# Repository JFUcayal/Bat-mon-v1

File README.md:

# Bat-mon-v1
**Edge Device for Battery Environment Monitoring System (Lithium Storage and Transport)**

- **Bat-Mon** is a hardware/firmware project developed as part of my Master's thesis in an industrial environment at [b.again](https://b.again.pt/pt_PT/) [(dstgroup)](https://www.dstsgps.com/intro-pt-pt/#/#intro), focused on the real-time monitoring of lithium batteries. 
- It includes custom-designed PCBs for fixed and portable use cases, enabling the detection of environmental conditions such as **temperature**, **humidity**, and **vibration**. All hardware was developed using **KiCAD**.
- This project was developed in the context of a national R&D consortium for advanced energy storage systems:  
[New Generation Storage](https://newgenstorage.pt). It is partially funded by the **PRR – Recovery and Resilience Plan** and aims to support innovation in battery safety and smart monitoring systems.

## 🔧 Project Overview

Lithium batteries, whether in stationary storage or during transport, require careful environmental monitoring to ensure safety. Bat-Mon addresses this need by providing two types of monitoring devices:

- **Stationary Unit**: Designed for static storage. Measures temperature and humidity.
- **Portable Unit**: Designed for battery transport scenarios. Measures temperature, humidity, and vibration.

Both units support low-power operation and are intended to be integrated into broader telemetry or management systems.

## 📟 3D Views of the PCBs
<div id="image-table" align="center">
    <table>
        <tr>
            <td style="padding:10px"> <strong>📦 Stationary Monitoring Prototype</strong><br/><br/>
                
            </td>
            <td style="padding:10px"> <br/><strong>🚚 Portable Monitoring Prototype</strong><br/><br/>
                 
            </td>
        </tr>
    </table>
</div>
    
## 🚀 Key Features

- 🌡️ **Temperature and Humidity Sensing**
- 📈 **Vibration Detection** (portable unit)
- 📶 **BLE Communication Support**
- 🔋 **Low Power Design**
- 📐 **Designed in KiCAD**
- 🧠 **Powered by STM32**

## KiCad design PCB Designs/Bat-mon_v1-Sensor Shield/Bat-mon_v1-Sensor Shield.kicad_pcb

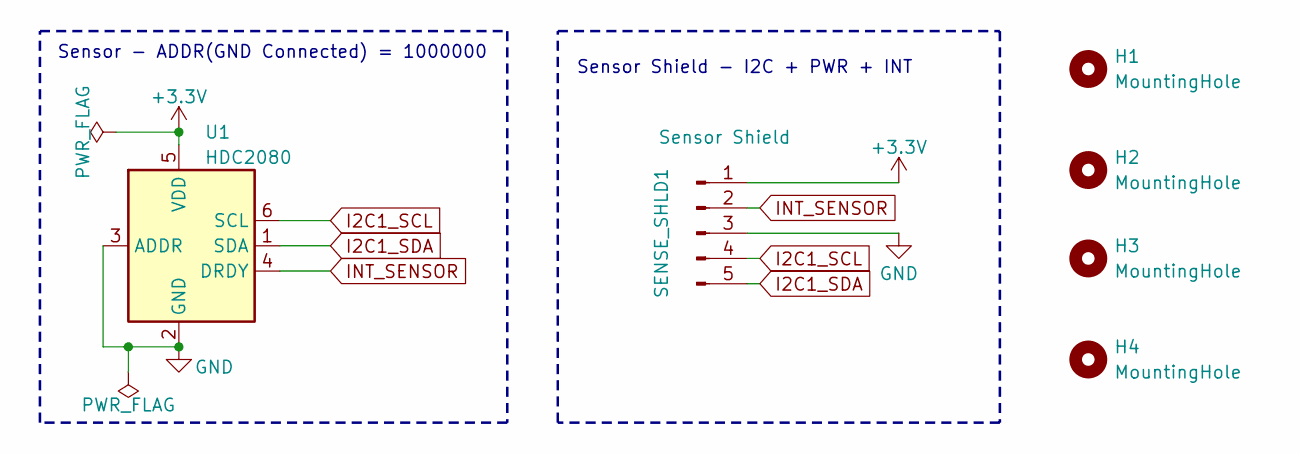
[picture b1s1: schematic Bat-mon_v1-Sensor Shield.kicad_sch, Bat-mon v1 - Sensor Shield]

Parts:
H1, H2, H3, H4: MountingHole; MountingHole_2.2mm_M2_Pad_Via
SENSE_SHLD1: Sensor Shield; SHDR5W64P0X250_1X5_1490X575X700P
U1: HDC2080; Texas_PWSON-N6

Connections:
+3.3V: SENSE_SHLD1.1, U1.5 (VDD)
GND: SENSE_SHLD1.3, U1.2 (GND), U1.3 (ADDR)
I2C1_SCL: SENSE_SHLD1.4, U1.6 (SCL)
I2C1_SDA: SENSE_SHLD1.5, U1.1 (SDA)
INT_SENSOR: SENSE_SHLD1.2, U1.4 (DRDY)

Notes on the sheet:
Sensor - ADDR(GND Connected) = 1000000
Sensor Shield - I2C + PWR + INT

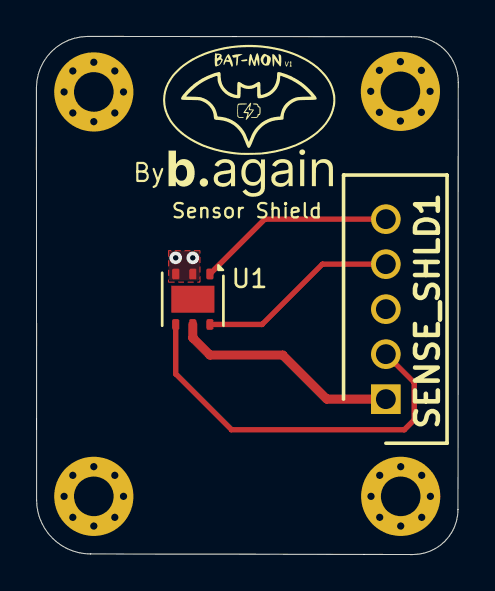
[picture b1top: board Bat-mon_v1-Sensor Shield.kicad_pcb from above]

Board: 2 copper layers, 23.4 x 28.8 mm, 6 parts (0 on the bottom side), 5 nets.

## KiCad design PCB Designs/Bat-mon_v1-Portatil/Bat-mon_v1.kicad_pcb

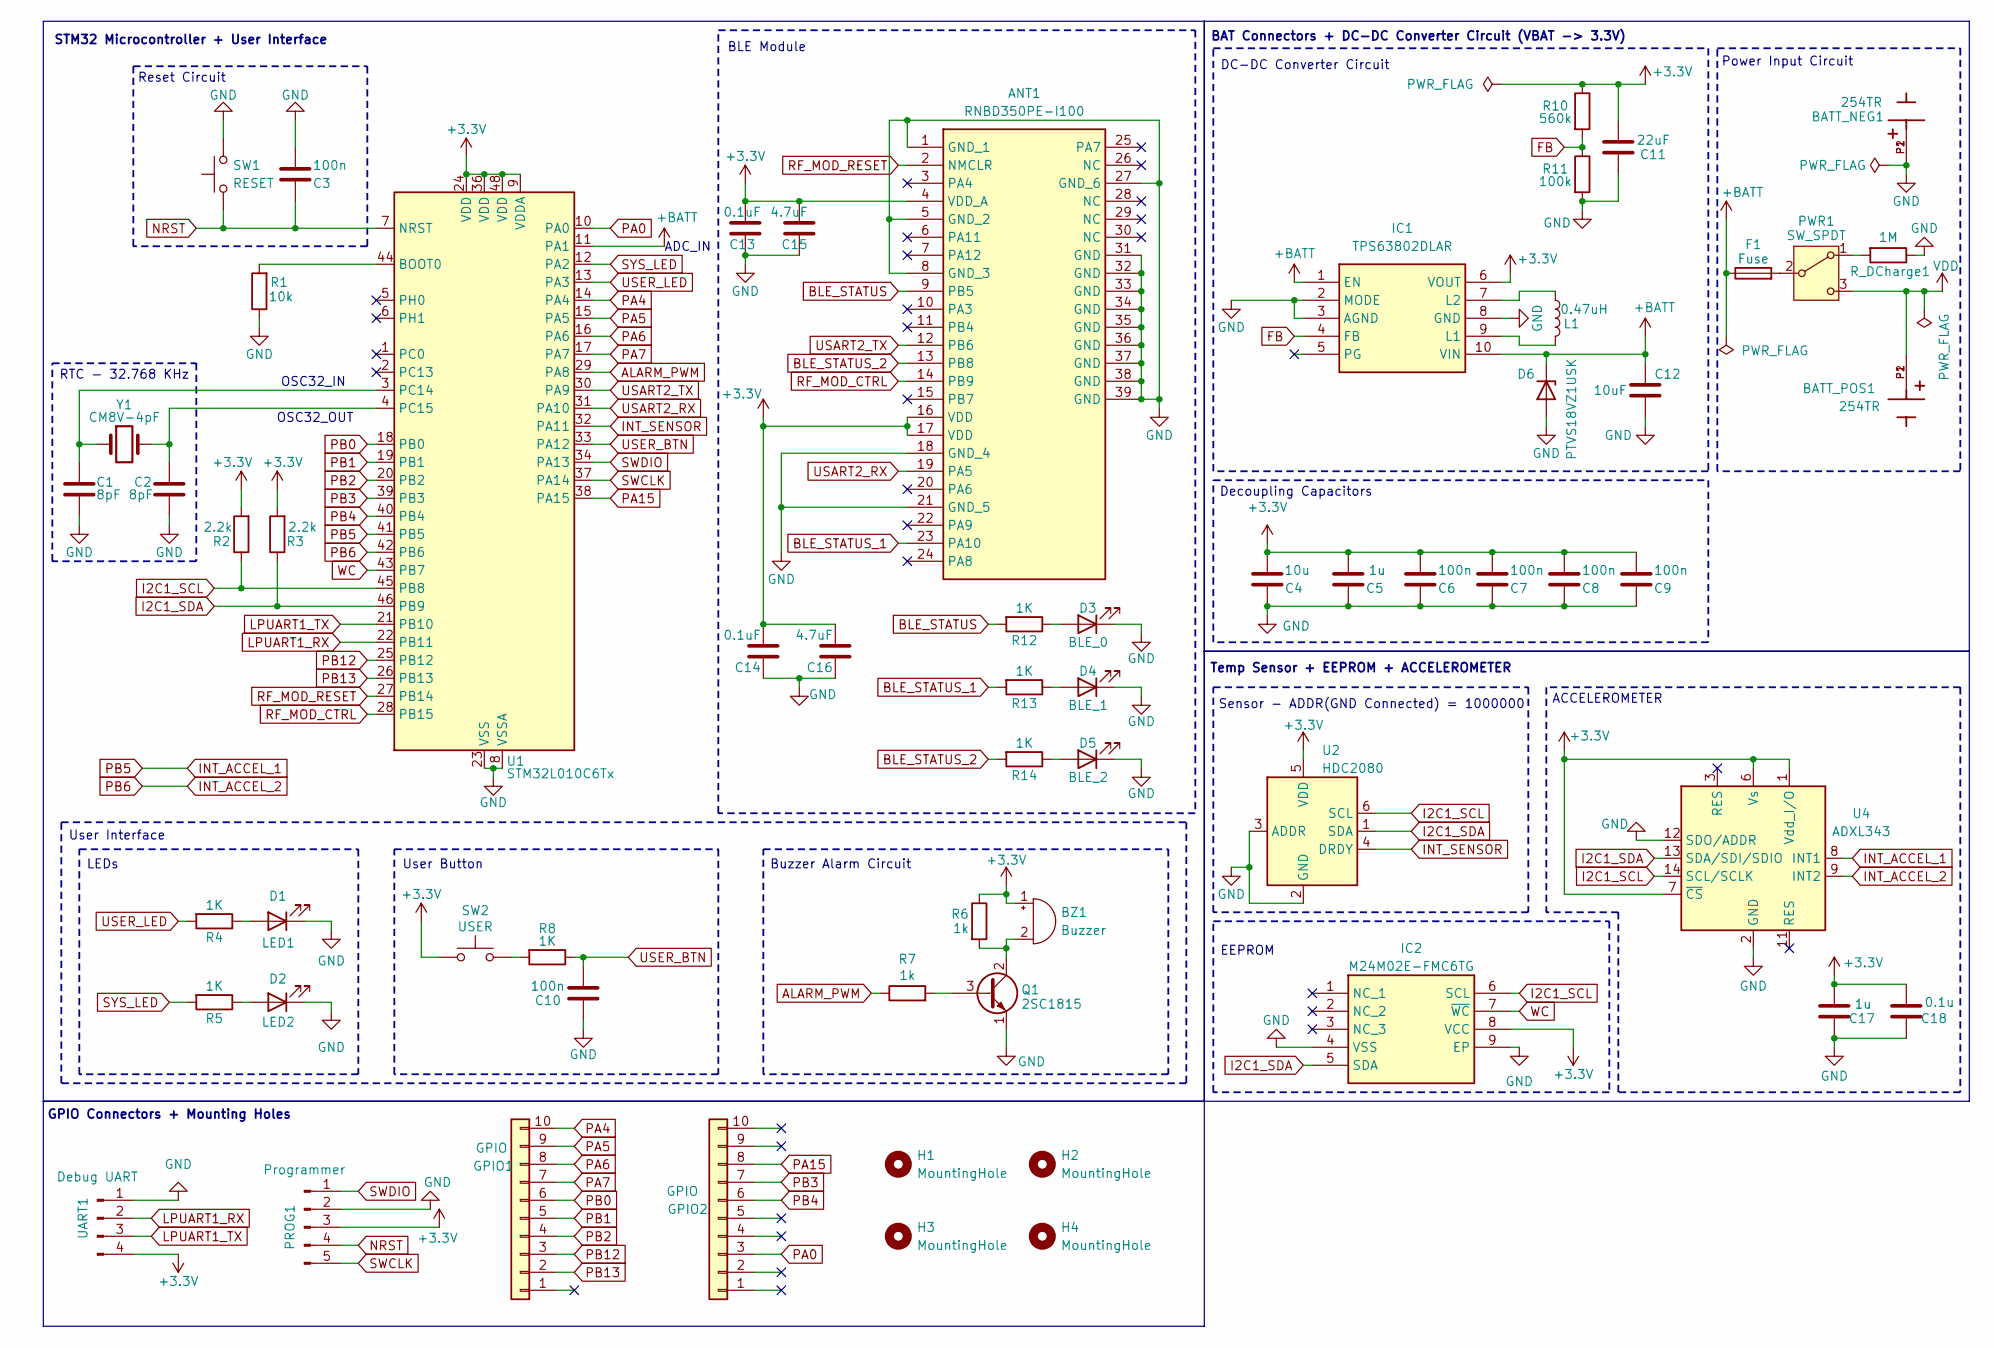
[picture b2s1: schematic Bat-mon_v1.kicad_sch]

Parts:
ANT1: RNBD350PE-I100; RNBD350PE-I100 - BLE Module; Manufacturer_Part_Number RNBD451PE-I100; Mouser Part Number 579-RNBD451PE-I100
BATT_NEG1: 254TR; BAT_254TR; PARTREV C
BATT_POS1: 254TR; BAT_254TR; PARTREV C
BZ1: Buzzer; PS17_1
C1, C2: 8pF; C_Disc_D3.4mm_W2.1mm_P2.50mm
C3, C6, C7, C8, C9, C10: 100n; C_Disc_D3.4mm_W2.1mm_P2.50mm
C4: 10u; C_Disc_D3.4mm_W2.1mm_P2.50mm
C5, C17: 1u; C_Disc_D3.4mm_W2.1mm_P2.50mm
C11: 22uF; C_Disc_D3.4mm_W2.1mm_P2.50mm
C12: 10uF; C_Disc_D3.4mm_W2.1mm_P2.50mm
C13, C14: 0.1uF; C_Disc_D3.4mm_W2.1mm_P2.50mm
C15, C16: 4.7uF; C_Disc_D3.4mm_W2.1mm_P2.50mm
C18: 0.1u; C_Disc_D3.4mm_W2.1mm_P2.50mm
D1: LED1; LEDC1608X80N
D2: LED2; LEDC1608X80N
D3: BLE_0; LEDC1608X80N
D4: BLE_1; LEDC1608X80N
D5: BLE_2; LEDC1608X80N
D6: PTVS18VZ1USK; SODFL4725X105N
F1: Fuse; WR-FSH_THT_2
GPIO1, GPIO2: GPIO; Header_F_1X10_61301011821
H1, H2, H3, H4: MountingHole; MountingHole_2.2mm_M2_Pad_Via
IC1: TPS63802DLAR; Mouser Part Number 595-TPS63802DLAR
IC2: M24M02E-FMC6TG; M24M02EFMC6TG; Mouser Part Number 511-M24M02E-FMC6TG
L1: 0.47uH; L_Axial_L5.3mm_D2.2mm_P7.62mm_Horizontal_Vishay_IM-1
PROG1: Programmer; PinHeader_1x05_P2.54mm_Vertical
PWR1: SW_SPDT; SLW2327758AND
Q1: 2SC1815; TO-92_Inline
R1: 10k; R_Axial_DIN0207_L6.3mm_D2.5mm_P7.62mm_Horizontal
R2, R3: 2.2k; R_Axial_DIN0207_L6.3mm_D2.5mm_P7.62mm_Horizontal
R4, R5, R8, R12, R13, R14: 1K; R_Axial_DIN0207_L6.3mm_D2.5mm_P7.62mm_Horizontal
R6, R7: 1k; R_Axial_DIN0207_L6.3mm_D2.5mm_P7.62mm_Horizontal
R10: 560k; R_Axial_DIN0207_L6.3mm_D2.5mm_P7.62mm_Horizontal
R11: 100k; R_Axial_DIN0207_L6.3mm_D2.5mm_P7.62mm_Horizontal
R_DCharge1: 1M; R_Axial_DIN0207_L6.3mm_D2.5mm_P7.62mm_Horizontal
SW1: RESET; SW_Push_SPST_NO_Alps_SKRK
SW2: USER; SW_Push_SPST_NO_Alps_SKRK
U1: STM32L010C6Tx; LQFP-48_7x7mm_P0.5mm
U2: HDC2080; Texas_PWSON-N6
U4: ADXL343; LGA-14_3x5mm_P0.8mm_LayoutBorder1x6y
UART1: Debug UART; Header_M_1X4_61300411121
Y1: CM8V-4pF; Crystal_SMD_MicroCrystal_CC8V-T1A-2Pin_2.0x1.2mm

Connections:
+3.3V: ANT1.4 (VDD_A), ANT1.16 (VDD), ANT1.17 (VDD), BZ1.1 (+), C4.2, C5.2, C6.2, C7.2, C8.2, C9.2, C11.2, C13.2, C14.2, C15.2, C16.2, C17.2, C18.2, IC1.6 (VOUT), IC2.8 (VCC), PROG1.3, R2.2, R3.2, R6.1, R10.1, SW2.1, U1.9 (VDDA), U1.24 (VDD), U1.36 (VDD), U1.48 (VDD), U2.5 (VDD), U4.1 (Vdd_I/O), U4.6 (Vs), U4.7 (~CS), UART1.4
+BATT: C12.2, D6.1 (K), F1.1, IC1.1 (EN), IC1.10 (VIN), U1.11 (PA1)
ALARM_PWM: R7.1, U1.29 (PA8)
BLE_STATUS: ANT1.9 (PB5), R12.2
BLE_STATUS_1: ANT1.23 (PA10), R13.2
BLE_STATUS_2: ANT1.13 (PB8), R14.2
FB: IC1.4 (FB), R10.2, R11.1
GND: ANT1.1 (GND_1), ANT1.5 (GND_2), ANT1.8 (GND_3), ANT1.18 (GND_4), ANT1.21 (GND_5), ANT1.27 (GND_6), ANT1.31 (GND), ANT1.32 (GND), ANT1.33 (GND), ANT1.34 (GND), ANT1.35 (GND), ANT1.36 (GND), ANT1.37 (GND), ANT1.38 (GND), ANT1.39 (GND), BATT_NEG1.P1, BATT_NEG1.P2, C1.2, C2.2, C3.2, C4.1, C5.1, C6.1, C7.1, C8.1, C9.1, C10.1, C11.1, C12.1, C13.1, C14.1, C15.1, C16.1, C17.1, C18.1, D1.1 (K), D2.1 (K), D3.1 (K), D4.1 (K), D5.1 (K), D6.2 (A), IC1.2 (MODE), IC1.3 (AGND), IC1.8 (GND), IC2.4 (VSS), IC2.9 (EP), PROG1.2, Q1.1 (E), R1.1, R11.2, R_DCharge1.1, SW1.2, U1.8 (VSSA), U1.23 (VSS), U1.35 (VSS), U1.47 (VSS), U2.2 (GND), U2.3 (ADDR), U4.2 (GND), U4.4 (GND), U4.5 (GND), U4.12 (SDO/ADDR), UART1.1
I2C1_SCL: IC2.6 (SCL), R2.1, U1.45 (PB8), U2.6 (SCL), U4.14 (SCL/SCLK)
I2C1_SDA: IC2.5 (SDA), R3.1, U1.46 (PB9), U2.1 (SDA), U4.13 (SDA/SDI/SDIO)
INT_ACCEL_1: U1.41 (PB5), U4.8 (INT1)
INT_ACCEL_2: U1.42 (PB6), U4.9 (INT2)
INT_SENSOR: U1.32 (PA11), U2.4 (DRDY)
LPUART1_RX: U1.22 (PB11), UART1.2
LPUART1_TX: U1.21 (PB10), UART1.3
NRST: C3.1, PROG1.4, SW1.1, U1.7 (NRST)
unnamed: BZ1.2 (-), Q1.2 (C), R6.2
unnamed: D1.2 (A), R4.1
unnamed: D2.2 (A), R5.1
unnamed: D3.2 (A), R12.1
unnamed: D4.2 (A), R13.1
unnamed: D5.2 (A), R14.1
unnamed: IC1.9 (L1), L1.2
unnamed: IC1.7 (L2), L1.1
unnamed: PWR1.1 (A), R_DCharge1.2
unnamed: F1.2, PWR1.2 (B)
unnamed: Q1.3 (B), R7.2
unnamed: R8.2, SW2.2
unnamed: R1.2, U1.44 (BOOT0)
unnamed: C1.1, U1.3 (PC14), Y1.1
unnamed: C2.1, U1.4 (PC15), Y1.2
PA0: GPIO2.3, U1.10 (PA0)
PA4: GPIO1.10, U1.14 (PA4)
PA5: GPIO1.9, U1.15 (PA5)
PA6: GPIO1.8, U1.16 (PA6)
PA7: GPIO1.7, U1.17 (PA7)
PA15: GPIO2.8, U1.38 (PA15)
PB0: GPIO1.6, U1.18 (PB0)
PB1: GPIO1.5, U1.19 (PB1)
PB2: GPIO1.4, U1.20 (PB2)
PB3: GPIO2.7, U1.39 (PB3)
PB4: GPIO2.6, U1.40 (PB4)
PB12: GPIO1.3, U1.25 (PB12)
PB13: GPIO1.2, U1.26 (PB13)
RF_MOD_CTRL: ANT1.14 (PB9), U1.28 (PB15)
RF_MOD_RESET: ANT1.2 (NMCLR), U1.27 (PB14)
SWCLK: PROG1.5, U1.37 (PA14)
SWDIO: PROG1.1, U1.34 (PA13)
SYS_LED: R5.2, U1.12 (PA2)
USART2_RX: ANT1.19 (PA5), U1.31 (PA10)
USART2_TX: ANT1.12 (PB6), U1.30 (PA9)
USER_BTN: C10.2, R8.1, U1.33 (PA12)
USER_LED: R4.2, U1.13 (PA3)
VDD: BATT_POS1.P1, BATT_POS1.P2, PWR1.3 (C)
WC: IC2.7 (~WC), U1.43 (PB7)

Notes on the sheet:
EEPROM
GPIO Connectors + Mounting Holes
BLE Module
User Button
RTC - 32.768 KHz
User Interface
LEDs
BAT Connectors + DC-DC Converter Circuit (VBAT -> 3.3V)
Sensor - ADDR(GND Connected) = 1000000
DC-DC Converter Circuit
STM32 Microcontroller + User Interface
OSC32_IN
Temp Sensor + EEPROM + ACCELEROMETER
OSC32_OUT
ADC_IN
Buzzer Alarm Circuit
Decoupling Capacitors
Power Input Circuit
ACCELEROMETER
Reset Circuit

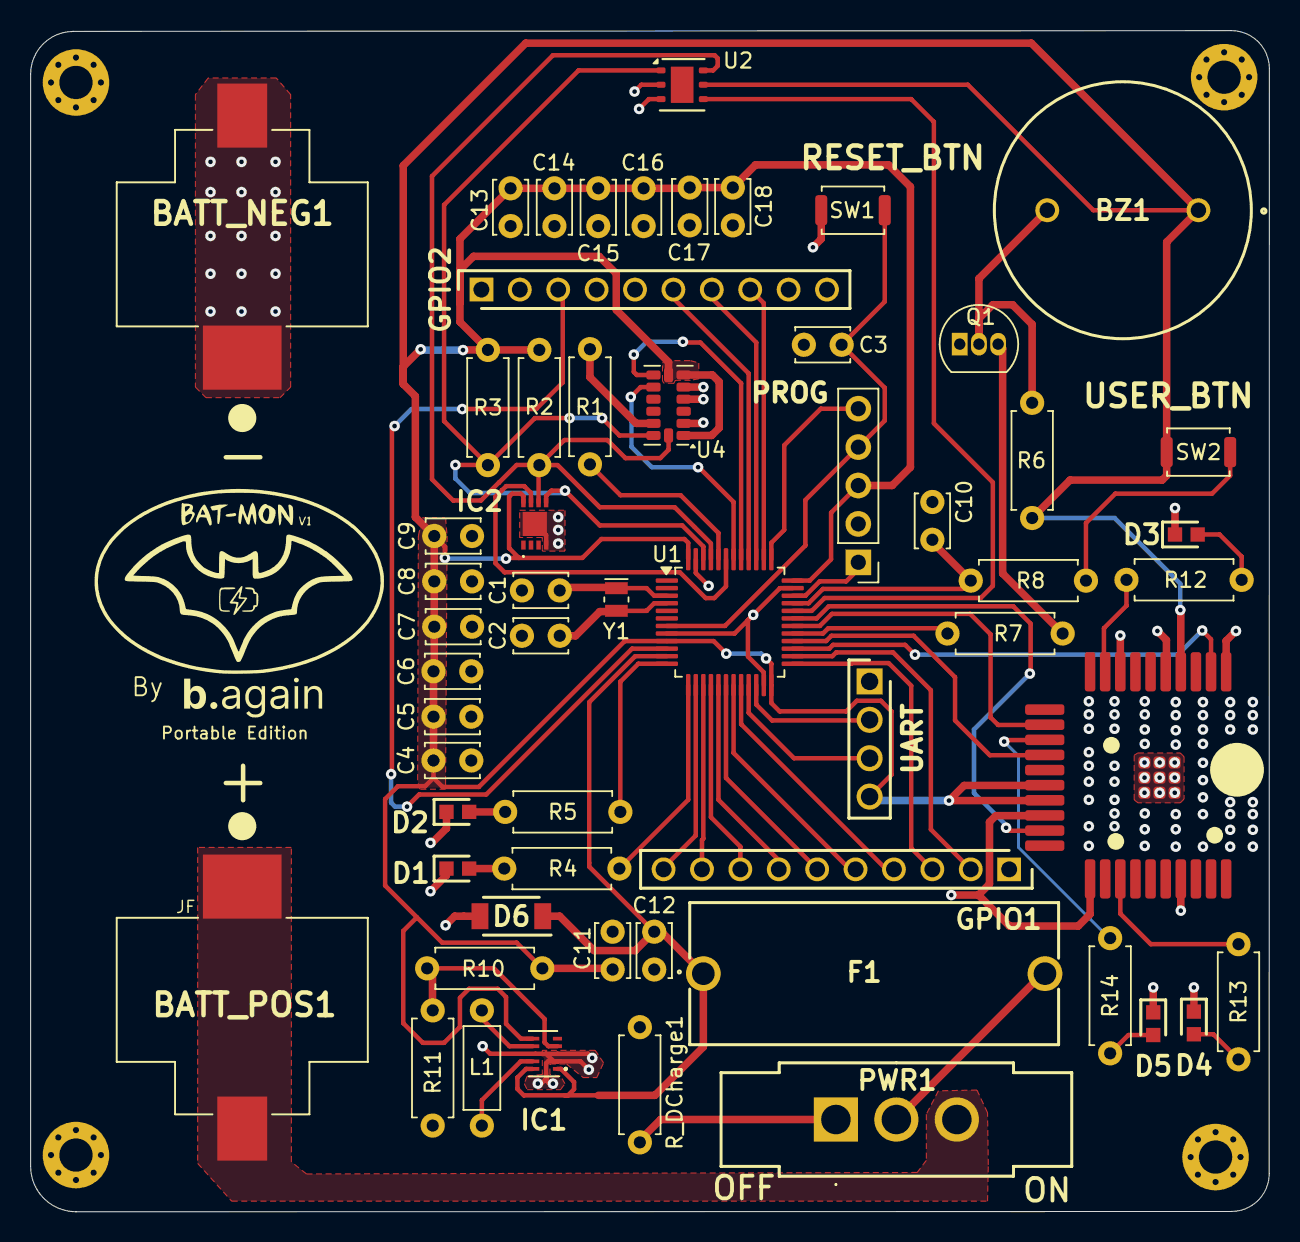
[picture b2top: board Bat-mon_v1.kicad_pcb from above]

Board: 2 copper layers, 81.9 x 78.1 mm, 62 parts (0 on the bottom side), 55 nets.

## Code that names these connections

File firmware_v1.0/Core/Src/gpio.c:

/* USER CODE BEGIN Header */
/**
  ******************************************************************************
  * @file    gpio.c
  * @brief   This file provides code for the configuration
  *          of all used GPIO pins.
  ******************************************************************************
  * @attention
  *
  * Copyright (c) 2025 STMicroelectronics.
  * All rights reserved.
  *
  * This software is licensed under terms that can be found in the LICENSE file
  * in the root directory of this software component.
  * If no LICENSE file comes with this software, it is provided AS-IS.
  *
  ******************************************************************************
  */
/* USER CODE END Header */

/* Includes ------------------------------------------------------------------*/
#include "gpio.h"

/* USER CODE BEGIN 0 */

/* USER CODE END 0 */

/*----------------------------------------------------------------------------*/
/* Configure GPIO                                                             */
/*----------------------------------------------------------------------------*/
/* USER CODE BEGIN 1 */

/* USER CODE END 1 */

/** Configure pins as
        * Analog
        * Input
        * Output
        * EVENT_OUT
        * EXTI
*/
void MX_GPIO_Init(void)
{

  GPIO_InitTypeDef GPIO_InitStruct = {0};

  /* GPIO Ports Clock Enable */
  __HAL_RCC_GPIOC_CLK_ENABLE();
  __HAL_RCC_GPIOA_CLK_ENABLE();
  __HAL_RCC_GPIOB_CLK_ENABLE();

  /*Configure GPIO pin Output Level */
  HAL_GPIO_WritePin(GPIOA, GPIO_PIN_2|GPIO_PIN_3, GPIO_PIN_RESET);

  /*Configure GPIO pins : PA2 PA3 */
  GPIO_InitStruct.Pin = GPIO_PIN_2|GPIO_PIN_3;
  GPIO_InitStruct.Mode = GPIO_MODE_OUTPUT_PP;
  GPIO_InitStruct.Pull = GPIO_NOPULL;
  GPIO_InitStruct.Speed = GPIO_SPEED_FREQ_LOW;
  HAL_GPIO_Init(GPIOA, &GPIO_InitStruct);

  /*Configure GPIO pins : PA11 PA12 */
  GPIO_InitStruct.Pin = GPIO_PIN_11|GPIO_PIN_12;
  GPIO_InitStruct.Mode = GPIO_MODE_IT_RISING;
  GPIO_InitStruct.Pull = GPIO_NOPULL;
  HAL_GPIO_Init(GPIOA, &GPIO_InitStruct);

  /*Configure GPIO pins : PB5 PB6 */
  GPIO_InitStruct.Pin = GPIO_PIN_5|GPIO_PIN_6;
  GPIO_InitStruct.Mode = GPIO_MODE_IT_RISING;
  GPIO_InitStruct.Pull = GPIO_NOPULL;
  HAL_GPIO_Init(GPIOB, &GPIO_InitStruct);

  /* EXTI interrupt init*/
  HAL_NVIC_SetPriority(EXTI4_15_IRQn, 0, 0);
  HAL_NVIC_EnableIRQ(EXTI4_15_IRQn);

}

/* USER CODE BEGIN 2 */

/* USER CODE END 2 */

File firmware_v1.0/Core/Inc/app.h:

/*
 * app.h
 *
 *  Created on: May 5, 2025
 *      Author: dst2001055
 */

#ifndef INC_APP_H_
#define INC_APP_H_

#include "mal.h"
//#include "system.h"
#include "sensors.h"
#include "logger.h"

// ----- Thresholds define --------
#define TEMP_HIGH_ALERT_VAL 35.00
#define HUM_HIGH_ALERT_VAL  79.00

// ----- App timing define --------
#define APP_DELAY 5000
#define DEBOUNCE_DELAY 100

// ----- GPIO define --------
#define USER_BTN GPIO_PIN_12
#define INT_HDC2080_PIN GPIO_PIN_11

#define USER_LED_PIN GPIO_PIN_3
#define SYS_LED_PIN GPIO_PIN_2

#define ALARM_PWM_PIN GPIO_PIN_8

// --------------------------------
enum states{IDLE, DATA_READ, COMMS, ANOMALY, RECONNECT, LOGS, CLEAN_MEM};

// CONFIG
uint8_t init_device();

// APPLICATION
void app_fsm();
uint8_t state_idle();
uint8_t state_read_sensors();
uint8_t state_comms();
uint8_t state_anomaly();
uint8_t state_reconnect();
uint8_t state_print_logs();
uint8_t state_clean_memory();

// ERROR
void error_handler(uint8_t error_code);


#endif /* INC_APP_H_ */

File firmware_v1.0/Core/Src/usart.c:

/* USER CODE BEGIN Header */
/**
  ******************************************************************************
  * @file    usart.c
  * @brief   This file provides code for the configuration
  *          of the USART instances.
  ******************************************************************************
  * @attention
  *
  * Copyright (c) 2025 STMicroelectronics.
  * All rights reserved.
  *
  * This software is licensed under terms that can be found in the LICENSE file
  * in the root directory of this software component.
  * If no LICENSE file comes with this software, it is provided AS-IS.
  *
  ******************************************************************************
  */
/* USER CODE END Header */
/* Includes ------------------------------------------------------------------*/
#include "usart.h"

/* USER CODE BEGIN 0 */

/* USER CODE END 0 */

UART_HandleTypeDef hlpuart1;

/* LPUART1 init function */

void MX_LPUART1_UART_Init(void)
{

  /* USER CODE BEGIN LPUART1_Init 0 */

  /* USER CODE END LPUART1_Init 0 */

  /* USER CODE BEGIN LPUART1_Init 1 */

  /* USER CODE END LPUART1_Init 1 */
  hlpuart1.Instance = LPUART1;
  hlpuart1.Init.BaudRate = 115200;
  hlpuart1.Init.WordLength = UART_WORDLENGTH_8B;
  hlpuart1.Init.StopBits = UART_STOPBITS_1;
  hlpuart1.Init.Parity = UART_PARITY_NONE;
  hlpuart1.Init.Mode = UART_MODE_TX_RX;
  hlpuart1.Init.HwFlowCtl = UART_HWCONTROL_NONE;
  hlpuart1.Init.OneBitSampling = UART_ONE_BIT_SAMPLE_DISABLE;
  hlpuart1.AdvancedInit.AdvFeatureInit = UART_ADVFEATURE_NO_INIT;
  if (HAL_UART_Init(&hlpuart1) != HAL_OK)
  {
    Error_Handler();
  }
  /* USER CODE BEGIN LPUART1_Init 2 */

  /* USER CODE END LPUART1_Init 2 */

}

void HAL_UART_MspInit(UART_HandleTypeDef* uartHandle)
{

  GPIO_InitTypeDef GPIO_InitStruct = {0};
  if(uartHandle->Instance==LPUART1)
  {
  /* USER CODE BEGIN LPUART1_MspInit 0 */

  /* USER CODE END LPUART1_MspInit 0 */
    /* LPUART1 clock enable */
    __HAL_RCC_LPUART1_CLK_ENABLE();

    __HAL_RCC_GPIOB_CLK_ENABLE();
    /**LPUART1 GPIO Configuration
    PB10     ------> LPUART1_TX
    PB11     ------> LPUART1_RX
    */
    GPIO_InitStruct.Pin = GPIO_PIN_10|GPIO_PIN_11;
    GPIO_InitStruct.Mode = GPIO_MODE_AF_PP;
    GPIO_InitStruct.Pull = GPIO_NOPULL;
    GPIO_InitStruct.Speed = GPIO_SPEED_FREQ_VERY_HIGH;
    GPIO_InitStruct.Alternate = GPIO_AF6_LPUART1;
    HAL_GPIO_Init(GPIOB, &GPIO_InitStruct);

  /* USER CODE BEGIN LPUART1_MspInit 1 */

  /* USER CODE END LPUART1_MspInit 1 */
  }
}

void HAL_UART_MspDeInit(UART_HandleTypeDef* uartHandle)
{

  if(uartHandle->Instance==LPUART1)
  {
  /* USER CODE BEGIN LPUART1_MspDeInit 0 */

  /* USER CODE END LPUART1_MspDeInit 0 */
    /* Peripheral clock disable */
    __HAL_RCC_LPUART1_CLK_DISABLE();

    /**LPUART1 GPIO Configuration
    PB10     ------> LPUART1_TX
    PB11     ------> LPUART1_RX
    */
    HAL_GPIO_DeInit(GPIOB, GPIO_PIN_10|GPIO_PIN_11);

  /* USER CODE BEGIN LPUART1_MspDeInit 1 */

  /* USER CODE END LPUART1_MspDeInit 1 */
  }
}

/* USER CODE BEGIN 1 */

/* USER CODE END 1 */

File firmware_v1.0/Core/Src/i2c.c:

/* USER CODE BEGIN Header */
/**
  ******************************************************************************
  * @file    i2c.c
  * @brief   This file provides code for the configuration
  *          of the I2C instances.
  ******************************************************************************
  * @attention
  *
  * Copyright (c) 2025 STMicroelectronics.
  * All rights reserved.
  *
  * This software is licensed under terms that can be found in the LICENSE file
  * in the root directory of this software component.
  * If no LICENSE file comes with this software, it is provided AS-IS.
  *
  ******************************************************************************
  */
/* USER CODE END Header */
/* Includes ------------------------------------------------------------------*/
#include "i2c.h"

/* USER CODE BEGIN 0 */

/* USER CODE END 0 */

I2C_HandleTypeDef hi2c1;

/* I2C1 init function */
void MX_I2C1_Init(void)
{

  /* USER CODE BEGIN I2C1_Init 0 */

  /* USER CODE END I2C1_Init 0 */

  /* USER CODE BEGIN I2C1_Init 1 */

  /* USER CODE END I2C1_Init 1 */
  hi2c1.Instance = I2C1;
  hi2c1.Init.Timing = 0x00000202;
  hi2c1.Init.OwnAddress1 = 0;
  hi2c1.Init.AddressingMode = I2C_ADDRESSINGMODE_7BIT;
  hi2c1.Init.DualAddressMode = I2C_DUALADDRESS_DISABLE;
  hi2c1.Init.OwnAddress2 = 0;
  hi2c1.Init.OwnAddress2Masks = I2C_OA2_NOMASK;
  hi2c1.Init.GeneralCallMode = I2C_GENERALCALL_DISABLE;
  hi2c1.Init.NoStretchMode = I2C_NOSTRETCH_DISABLE;
  if (HAL_I2C_Init(&hi2c1) != HAL_OK)
  {
    Error_Handler();
  }

  /** Configure Analogue filter
  */
  if (HAL_I2CEx_ConfigAnalogFilter(&hi2c1, I2C_ANALOGFILTER_ENABLE) != HAL_OK)
  {
    Error_Handler();
  }

  /** Configure Digital filter
  */
  if (HAL_I2CEx_ConfigDigitalFilter(&hi2c1, 0) != HAL_OK)
  {
    Error_Handler();
  }
  /* USER CODE BEGIN I2C1_Init 2 */

  /* USER CODE END I2C1_Init 2 */

}

void HAL_I2C_MspInit(I2C_HandleTypeDef* i2cHandle)
{

  GPIO_InitTypeDef GPIO_InitStruct = {0};
  if(i2cHandle->Instance==I2C1)
  {
  /* USER CODE BEGIN I2C1_MspInit 0 */

  /* USER CODE END I2C1_MspInit 0 */

    __HAL_RCC_GPIOB_CLK_ENABLE();
    /**I2C1 GPIO Configuration
    PB8     ------> I2C1_SCL
    PB9     ------> I2C1_SDA
    */
    GPIO_InitStruct.Pin = GPIO_PIN_8|GPIO_PIN_9;
    GPIO_InitStruct.Mode = GPIO_MODE_AF_OD;
    GPIO_InitStruct.Pull = GPIO_NOPULL;
    GPIO_InitStruct.Speed = GPIO_SPEED_FREQ_VERY_HIGH;
    GPIO_InitStruct.Alternate = GPIO_AF4_I2C1;
    HAL_GPIO_Init(GPIOB, &GPIO_InitStruct);

    /* I2C1 clock enable */
    __HAL_RCC_I2C1_CLK_ENABLE();
  /* USER CODE BEGIN I2C1_MspInit 1 */

  /* USER CODE END I2C1_MspInit 1 */
  }
}

void HAL_I2C_MspDeInit(I2C_HandleTypeDef* i2cHandle)
{

  if(i2cHandle->Instance==I2C1)
  {
  /* USER CODE BEGIN I2C1_MspDeInit 0 */

  /* USER CODE END I2C1_MspDeInit 0 */
    /* Peripheral clock disable */
    __HAL_RCC_I2C1_CLK_DISABLE();

    /**I2C1 GPIO Configuration
    PB8     ------> I2C1_SCL
    PB9     ------> I2C1_SDA
    */
    HAL_GPIO_DeInit(GPIOB, GPIO_PIN_8);

    HAL_GPIO_DeInit(GPIOB, GPIO_PIN_9);

  /* USER CODE BEGIN I2C1_MspDeInit 1 */

  /* USER CODE END I2C1_MspDeInit 1 */
  }
}

/* USER CODE BEGIN 1 */

/* USER CODE END 1 */

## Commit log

2025-09-15 First functional version of firmware
    - Temp + Hum + Accel Readings
    - Debug Logger with RTC timestamps (UART)
    - User Interface warning/status info via LEDs
    - HAL abstraction for modular MCU architectures
2025-10-15 BAT-SIGNAL - GUI w/ Temp + Hum + Accel (X,Y,Z)
